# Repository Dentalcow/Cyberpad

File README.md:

# Cyberpad
A 6 key, 2 encoder macro-pad with a smart LED lighting bar.

Initially, I was inspired to create this macropad by the neopixels found at the bottom of its board. These pixels can be used in a large number of ways; progress bars, volume, brightness and much more. This allowed me to center the design around minimalism and a two tone semi-transparent design.

Images from Cad:

Schematic:

PCB:

BOM:

- Six MX-style key swtches
- Six Blank DSA Keycaps
- Eight SK6812 MINI-E LEDs
- Two Rotary Encoders
- One Seeed XIAO RP2040
- One PCB
- One 3d Printed Case
- Four M3x16 Bolt
- Four M3 Heatset Insert

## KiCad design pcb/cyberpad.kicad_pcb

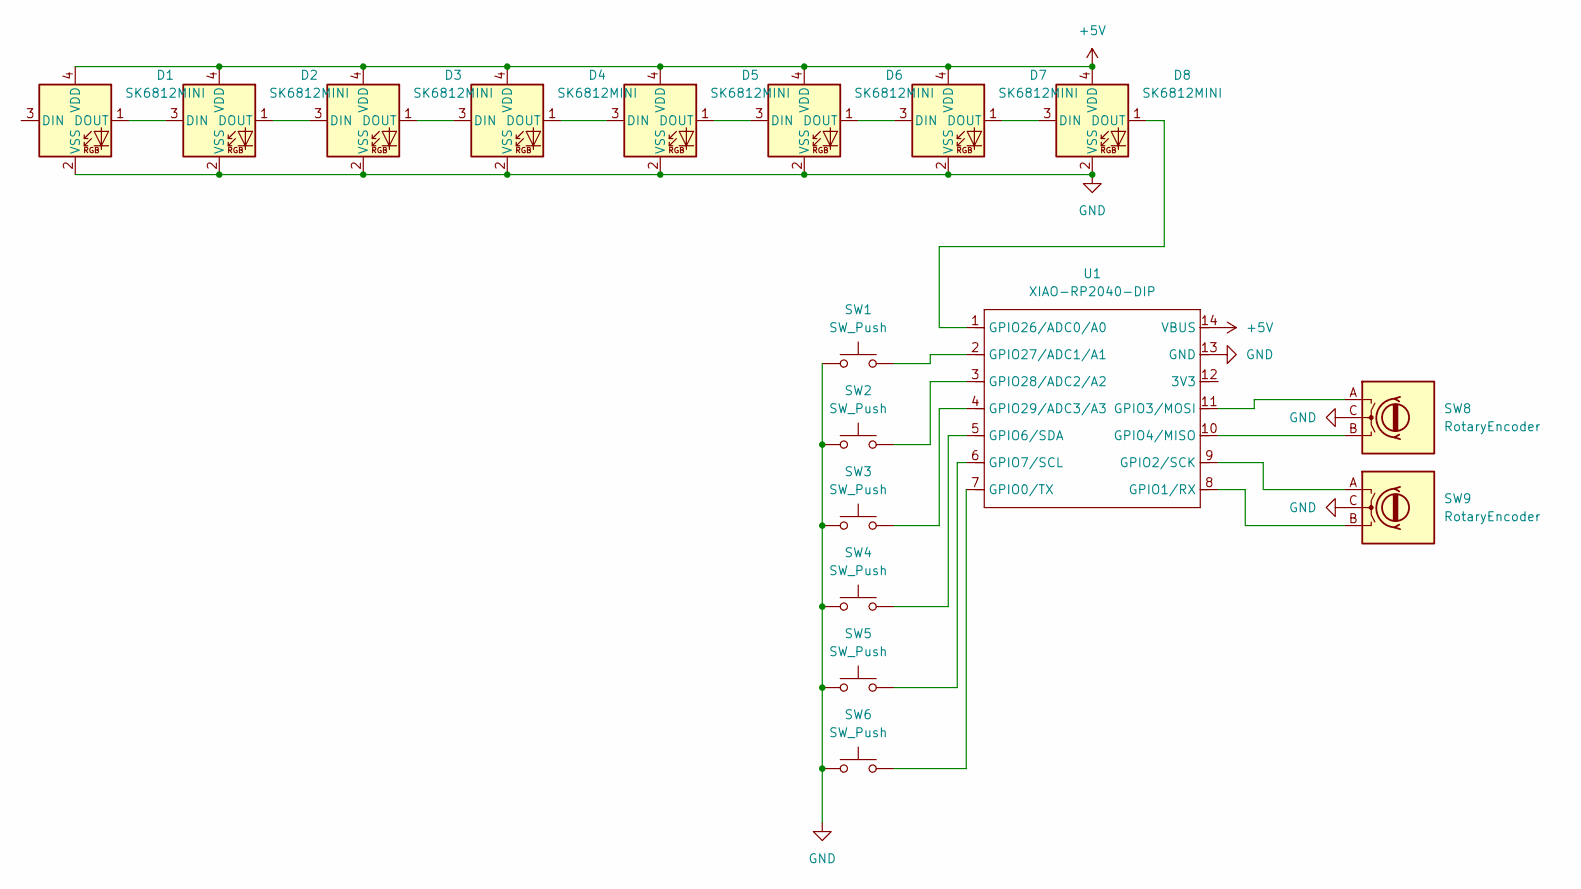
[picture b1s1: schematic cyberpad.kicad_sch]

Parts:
D1, D2, D3, D4, D5, D6, D7, D8: SK6812MINI; LED_SK6812MINI_PLCC4_3.5x3.5mm_P1.75mm
SW1, SW2, SW3, SW4, SW5, SW6: SW_Push; SW_Cherry_MX_1.00u_PCB
SW8, SW9: RotaryEncoder; RotaryEncoder_Alps_EC11E-Switch_Vertical_H20mm
U1: XIAO-RP2040-DIP

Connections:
+5V: D1.4 (VDD), D2.4 (VDD), D3.4 (VDD), D4.4 (VDD), D5.4 (VDD), D6.4 (VDD), D7.4 (VDD), D8.4 (VDD), U1.14 (VBUS)
GND: D1.2 (VSS), D2.2 (VSS), D3.2 (VSS), D4.2 (VSS), D5.2 (VSS), D6.2 (VSS), D7.2 (VSS), D8.2 (VSS), SW1.1, SW2.1, SW3.1, SW4.1, SW5.1, SW6.1, SW8.C, SW9.C, U1.13 (GND)
unnamed: D1.1 (DOUT), D2.3 (DIN)
unnamed: D2.1 (DOUT), D3.3 (DIN)
unnamed: D3.1 (DOUT), D4.3 (DIN)
unnamed: D4.1 (DOUT), D5.3 (DIN)
unnamed: D5.1 (DOUT), D6.3 (DIN)
unnamed: D6.1 (DOUT), D7.3 (DIN)
unnamed: D7.1 (DOUT), D8.3 (DIN)
unnamed: D8.1 (DOUT), U1.1 (GPIO26/ADC0/A0)
unnamed: SW6.2, U1.7 (GPIO0/TX)
unnamed: SW9.B, U1.8 (GPIO1/RX)
unnamed: SW9.A, U1.9 (GPIO2/SCK)
unnamed: SW8.A, U1.11 (GPIO3/MOSI)
unnamed: SW8.B, U1.10 (GPIO4/MISO)
unnamed: SW4.2, U1.5 (GPIO6/SDA)
unnamed: SW5.2, U1.6 (GPIO7/SCL)
unnamed: SW1.2, U1.2 (GPIO27/ADC1/A1)
unnamed: SW2.2, U1.3 (GPIO28/ADC2/A2)
unnamed: SW3.2, U1.4 (GPIO29/ADC3/A3)

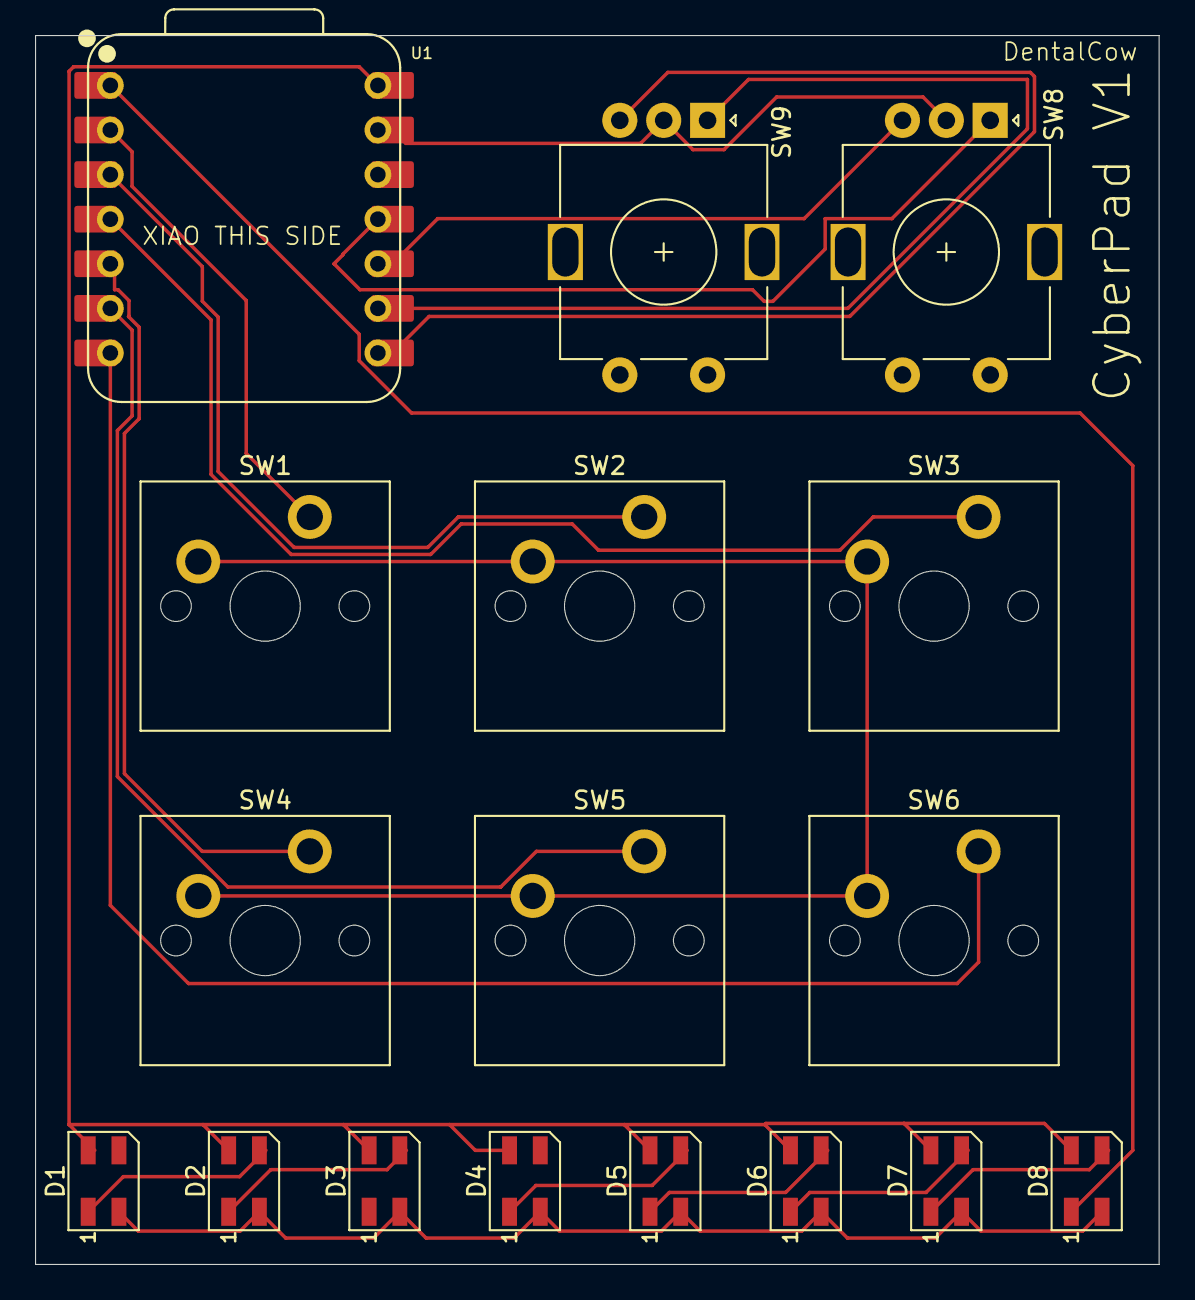
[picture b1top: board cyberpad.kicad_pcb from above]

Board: 2 copper layers, 64.0 x 70.0 mm, 17 parts (0 on the bottom side), 20 nets.

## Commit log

2025-11-30 Add CAD files for case
2025-11-30 Organisation, code and KiCad
2025-11-30 Enhance README with project details and images
    Expanded the README with project inspiration, images, schematic, PCB details, and BOM.
